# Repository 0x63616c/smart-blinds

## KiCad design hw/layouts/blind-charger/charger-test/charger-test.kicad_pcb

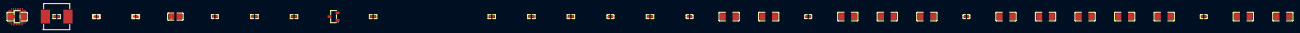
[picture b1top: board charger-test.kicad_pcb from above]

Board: 2 copper layers, 36 parts (0 on the bottom side), 19 nets, no tracks yet.

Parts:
C1, C2, C6, C7, C9, C10, C11, C15, C16, C17, C18, C19, C22: C1206
C3, C4, C5, C8, C12, C14, C20, C21: C0402
C13: C0805
L1: IND-SMD_L7.2-W6.6_GPSR07X0
Q1, Q2: SOT-23-3_L2.9-W1.3-P1.90-LS2.4-BR
R1, R2, R3, R4, R5, R6, R7, R8, R9, R10: R0402
U1: QFN-29_L4.0-W4.0-P0.40-TL-BQ25792RQMR

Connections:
2: C5.2, L1.2, U1.26
BATP: C3.1, R1.2, U1.18
CE_n: Q1.3, R2.2, U1.13
ILIM_HIZ: R4.1, R5.2, U1.17
PROG: R7.1, U1.20
SDRV: C14.1, U1.24
battery-hv: C1.1, C2.1, R1.1, U1.22, U1.23
c_boot1-1: C4.1, U1.4
c_boot1-1-1: C4.2, L1.1, U1.28
c_boot2-1: C5.1, U1.19
c_pmid1-1: C9.1, C10.1, C11.1, C12.1, C22.1, U1.29
c_regn-1: C13.1, R2.1, R5.1, R9.1, U1.5
charger-1: Q1.1, Q2.3, R3.1
charger-1-1: Q2.1, R6.2, R10.1
hv: Q2.2, R10.2
lv: C1.2, C2.2, C3.2, C6.2, C7.2, C8.2, C9.2, C10.2, C11.2, C12.2, C13.2, C14.2, C15.2, C16.2, C17.2, C18.2, C19.2, C20.2, C21.2, C22.2, Q1.2, R3.2, R4.2, R7.2, R8.2, U1.10, U1.11, U1.27
ntc: C21.1, R8.1, R9.2, U1.16
source-hv: C6.1, C7.1, C8.1, U1.2, U1.3, U1.8, U1.9
system-hv: C15.1, C16.1, C17.1, C18.1, C19.1, C20.1, U1.25

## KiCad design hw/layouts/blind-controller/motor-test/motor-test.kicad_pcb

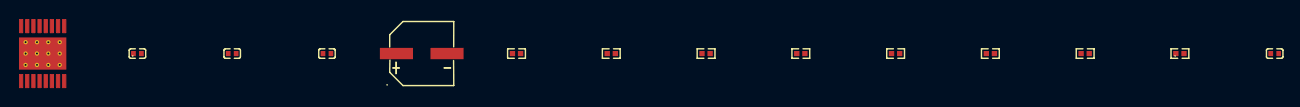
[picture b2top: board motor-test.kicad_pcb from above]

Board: 2 copper layers, 14 parts (0 on the bottom side), 13 nets, no tracks yet.

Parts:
C1: CAP-SMD_BD6.3-L6.6-W6.6-LS7.3-FD
C2, C3, C4, C5: C0402
R1, R2, R3, R4, R5, R6, R7, R8: R0402
U1: HTSSOP-16_L5.0-W4.4-P0.65-LS6.4-BL-EP

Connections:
1: C4.1, R6.2, R7.1, U1.5
CPH: C2.1, U1.13
CPL: C2.2, U1.14
IPROPI: R1.1, U1.6
PMODE: R5.2, U1.16
VCP: C3.1, U1.12
hv: R2.1, R5.1, R6.1
in1-1: R3.1, U1.1
in2-1: R4.1, U1.2
lv: C1.2, C4.2, C5.2, R1.2, R3.2, R4.2, R7.2, R8.2, U1.9, U1.15, U1.17
nFAULT: R2.2, U1.4
nSLEEP: R8.1, U1.3
pack-hv: C1.1, C3.2, C5.1, U1.11

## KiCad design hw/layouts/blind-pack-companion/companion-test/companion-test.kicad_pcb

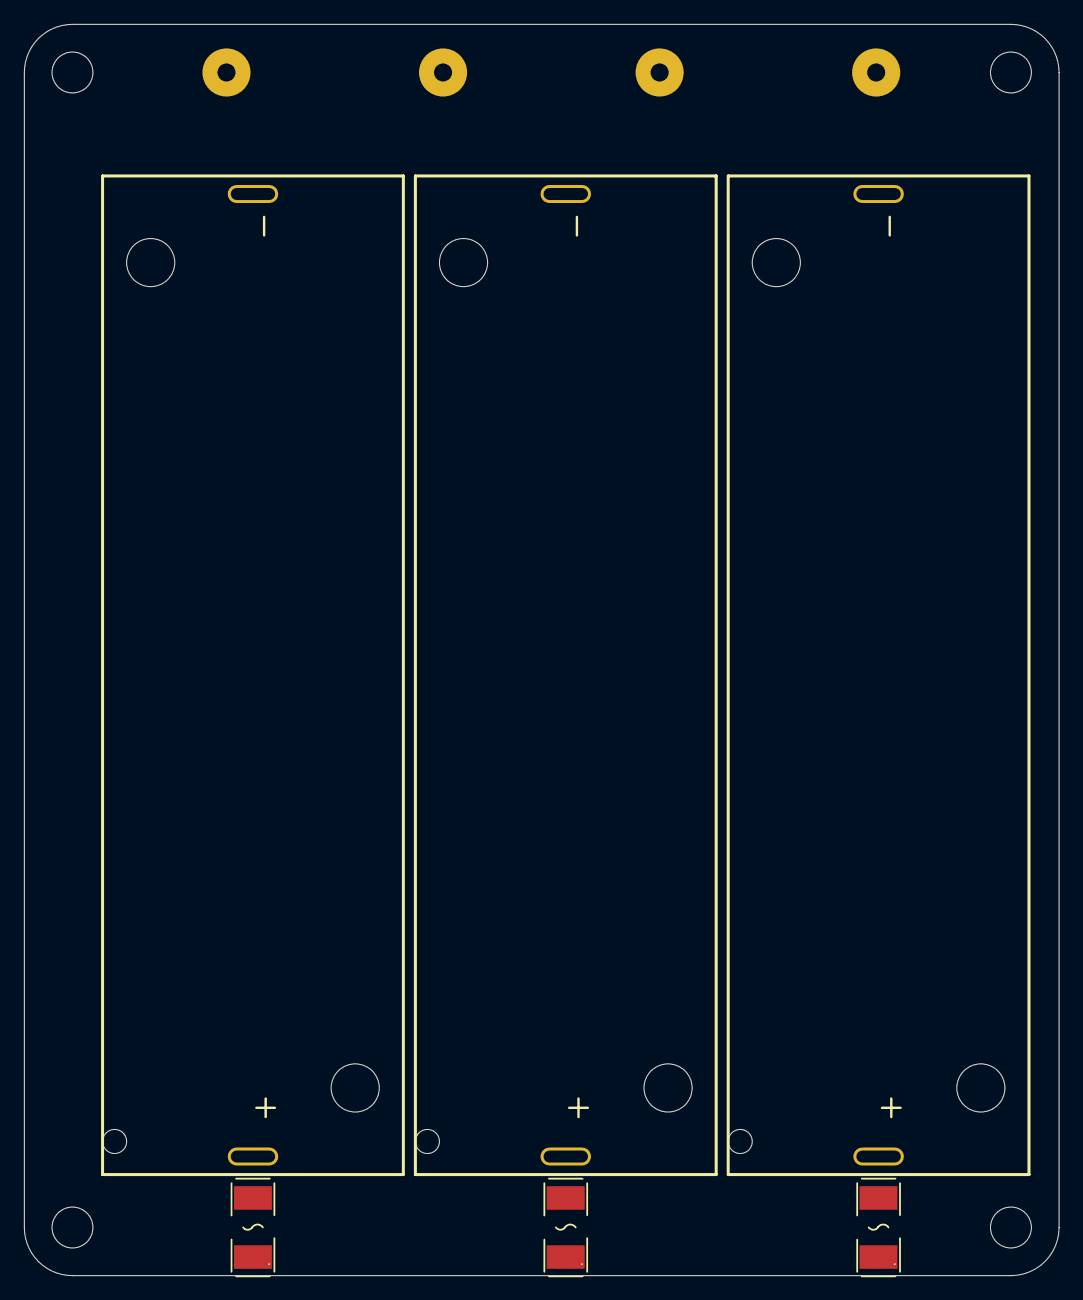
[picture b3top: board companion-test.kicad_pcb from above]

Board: 2 copper layers, 86.0 x 104.0 mm, 14 parts (0 on the bottom side), 7 nets, no tracks yet.

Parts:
BT1, BT2, BT3: BAT-TH_BH-21700-A5BJ001
F1, F2, F3: FUSE-SMD_L6.1-W2.7
H1, H2, H3, H4: M3 clearance 3.4 mm; MountingHole_M3_3.4mm
TP1, TP2, TP3, TP4: WirePad18

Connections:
1: BT1.1, F1.1
2: BT2.2, F1.2, TP1.1
carrier-1: BT2.1, F2.1
carrier-1-1: BT3.1, F3.1
carrier-2: BT3.2, F2.2, TP2.1
raw_ground: BT1.2, TP3.1
raw_top: F3.2, TP4.1

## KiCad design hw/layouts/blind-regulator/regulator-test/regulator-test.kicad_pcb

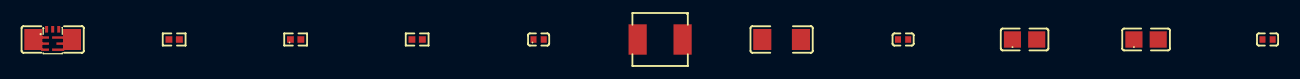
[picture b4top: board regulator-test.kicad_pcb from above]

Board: 2 copper layers, 12 parts (0 on the bottom side), 8 nets, no tracks yet.

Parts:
C1, C5, C6: C0402
C2, C7: C1206
C3, C4: C0805
L1: IND-SMD_L4.4-W4.2
R1, R2, R3: R0402
U1: VQFN-HR-9_L2.0-W1.5-P0.50-TL

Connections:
EN: R1.2, U1.5
MODE_S_CONF: R2.1, U1.7
PG: R3.2, U1.1
SS_TR: C6.1, U1.8
SW: L1.1, U1.2
hv: C1.1, C2.1, C7.1, R1.1, U1.6
logic-hv: C3.1, C4.1, C5.1, L1.2, R3.1, U1.3
lv: C1.2, C2.2, C3.2, C4.2, C5.2, C6.2, C7.2, R2.2, U1.4

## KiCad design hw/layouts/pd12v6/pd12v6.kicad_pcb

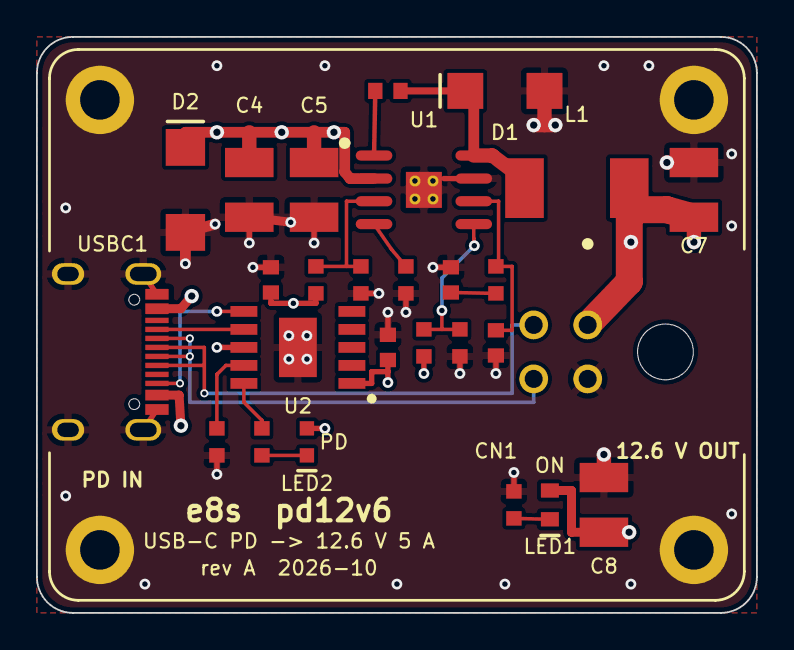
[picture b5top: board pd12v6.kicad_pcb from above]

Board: 4 copper layers, 40.0 x 32.0 mm, 31 parts (0 on the bottom side), 18 nets.

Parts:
C1, C2, C3, C6, C9: C0603
C4, C5, C7, C8: C1210
CN1: CONN-TH_0430450400
D1: SMA_L4.3-W2.6-LS5.2-RD
D2: SMB_L4.6-W3.6-LS5.3-RD
H1, H2, H3, H4: M2_HOLE
L1: IND-SMD_L7.1-W6.6
LED1: LED0603-RD_1
LED2: LED-SMD_L1.6-W0.8-R-RD
R1, R2, R3, R4, R5, R6, R7, R8, R9: R0603
U1: SOIC-8_L5.0-W4.0-P1.27-LS6.0-BL-EP2.0
U2: ESSOP-10_L4.9-W3.9-P1.0-LS6.0-TL-EP
USBC1: USB-C_SMD-TYPE-C-31-M-12_1

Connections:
BOOT: C1.1, U1.1
CC1: U2.7, USBC1.A5
CC2: U2.6, USBC1.B5
CFG1: R1.1, U2.9
COMP: C2.1, R2.1, U1.6
COMP_Z: C3.1, R2.2
EN: R8.2, R9.1, U1.3
FB: R3.2, R4.1, U1.5
GND: C2.2, C3.2, C4.2, C5.2, C6.2, C7.2, C8.2, C9.2, CN1.2, D1.2, D2.2, H1.1, H2.1, H3.1, H4.1, R1.2, R4.2, R5.2, R7.2, R9.2, U1.7, U1.9, U2.11, USBC1.1, USBC1.2, USBC1.3, USBC1.4, USBC1.A1B12, USBC1.B1A12
LED_OUT_K: LED1.1, R5.1
LED_PD_K: LED2.2, R6.1
PG_n: R6.2, U2.10
RT: R7.1, U1.4
SW: C1.2, D1.1, L1.1, U1.8
USB_DN: CN1.4, USBC1.A7, USBC1.B7
USB_DP: CN1.3, USBC1.A6, USBC1.B6
VBUS: C4.1, C5.1, C6.1, C9.1, D2.1, LED2.1, R8.1, U1.2, U2.1, U2.8, USBC1.A4B9, USBC1.B4A9
VOUT: C7.1, C8.1, CN1.1, L1.2, LED1.2, R3.1
